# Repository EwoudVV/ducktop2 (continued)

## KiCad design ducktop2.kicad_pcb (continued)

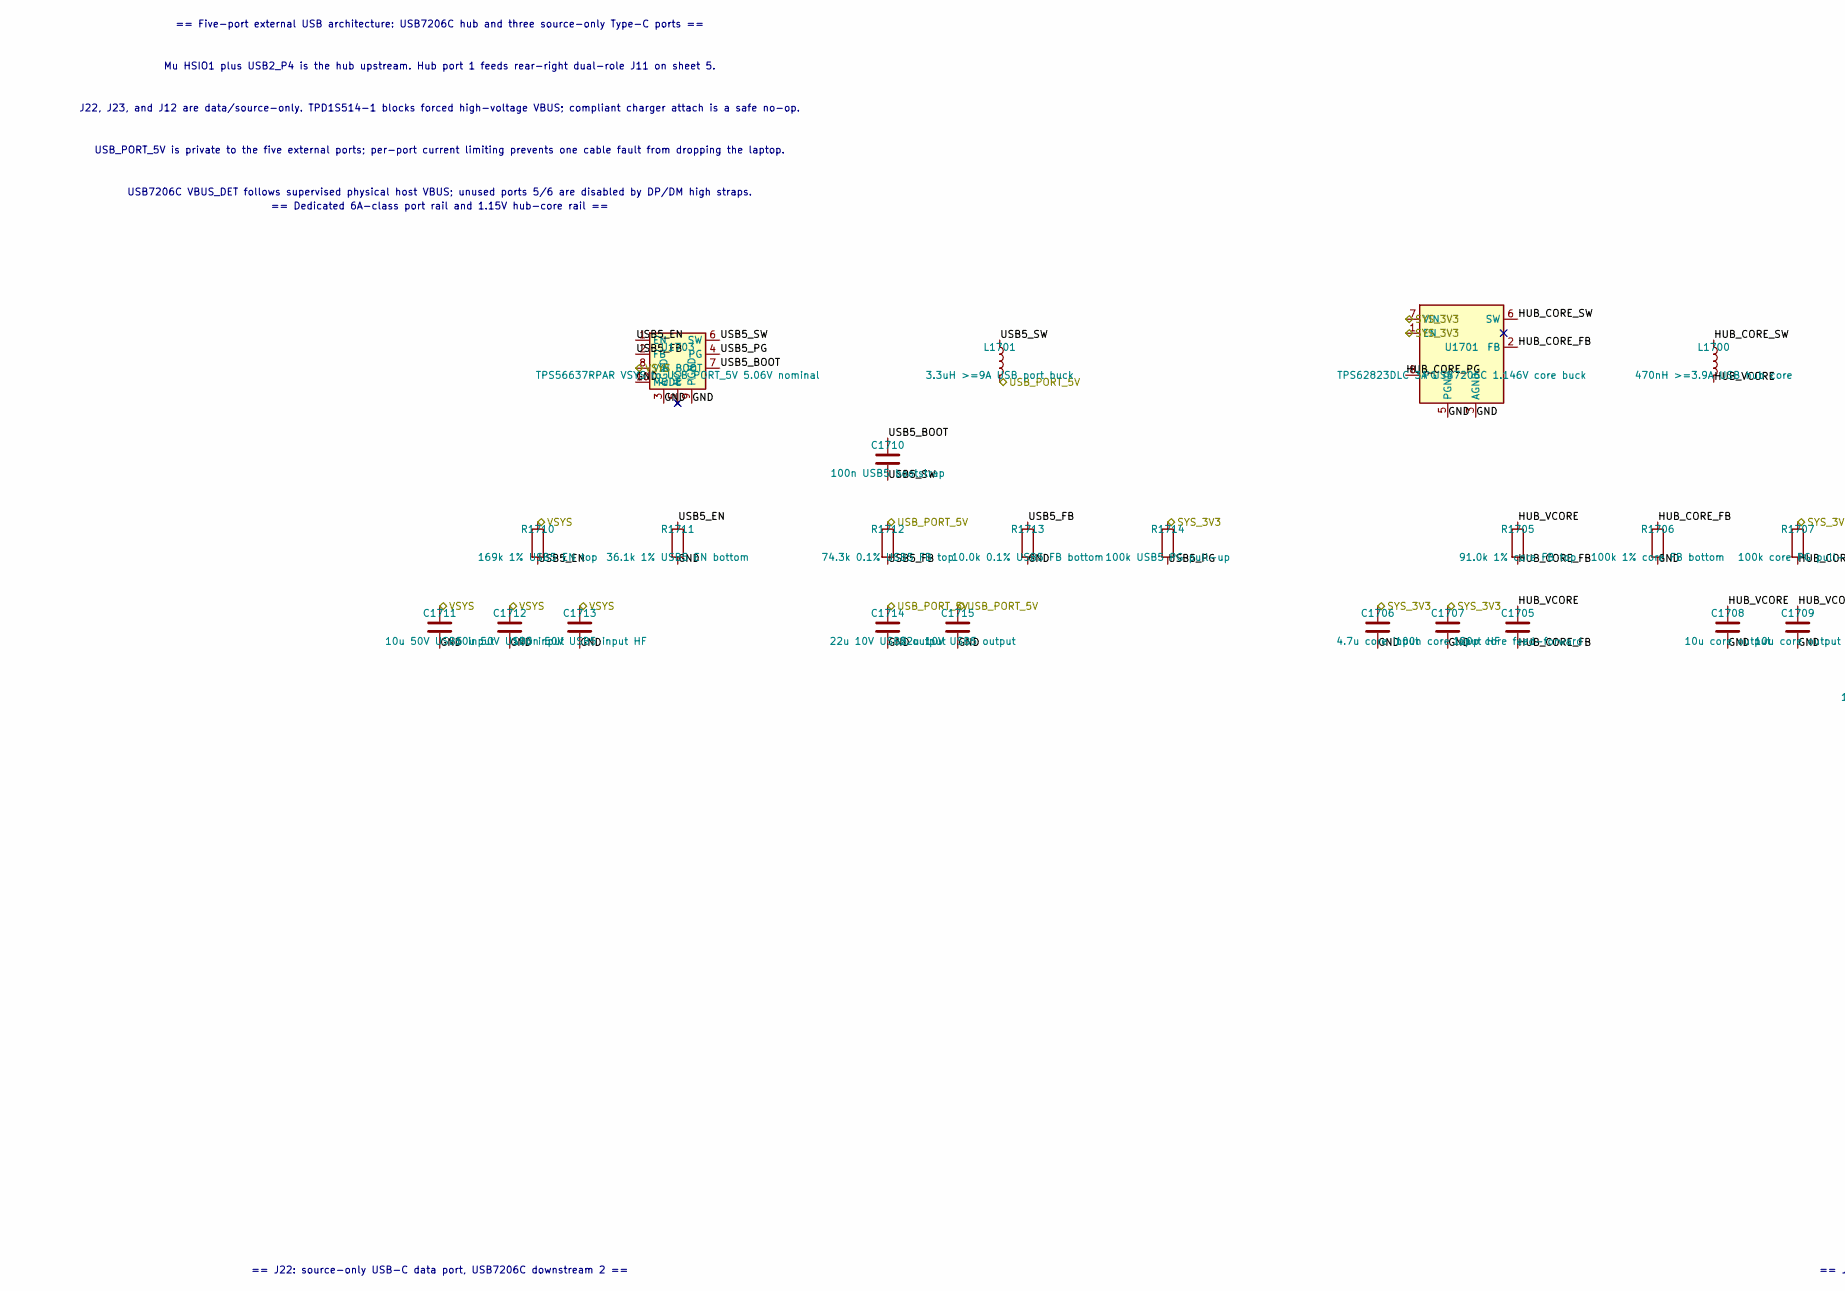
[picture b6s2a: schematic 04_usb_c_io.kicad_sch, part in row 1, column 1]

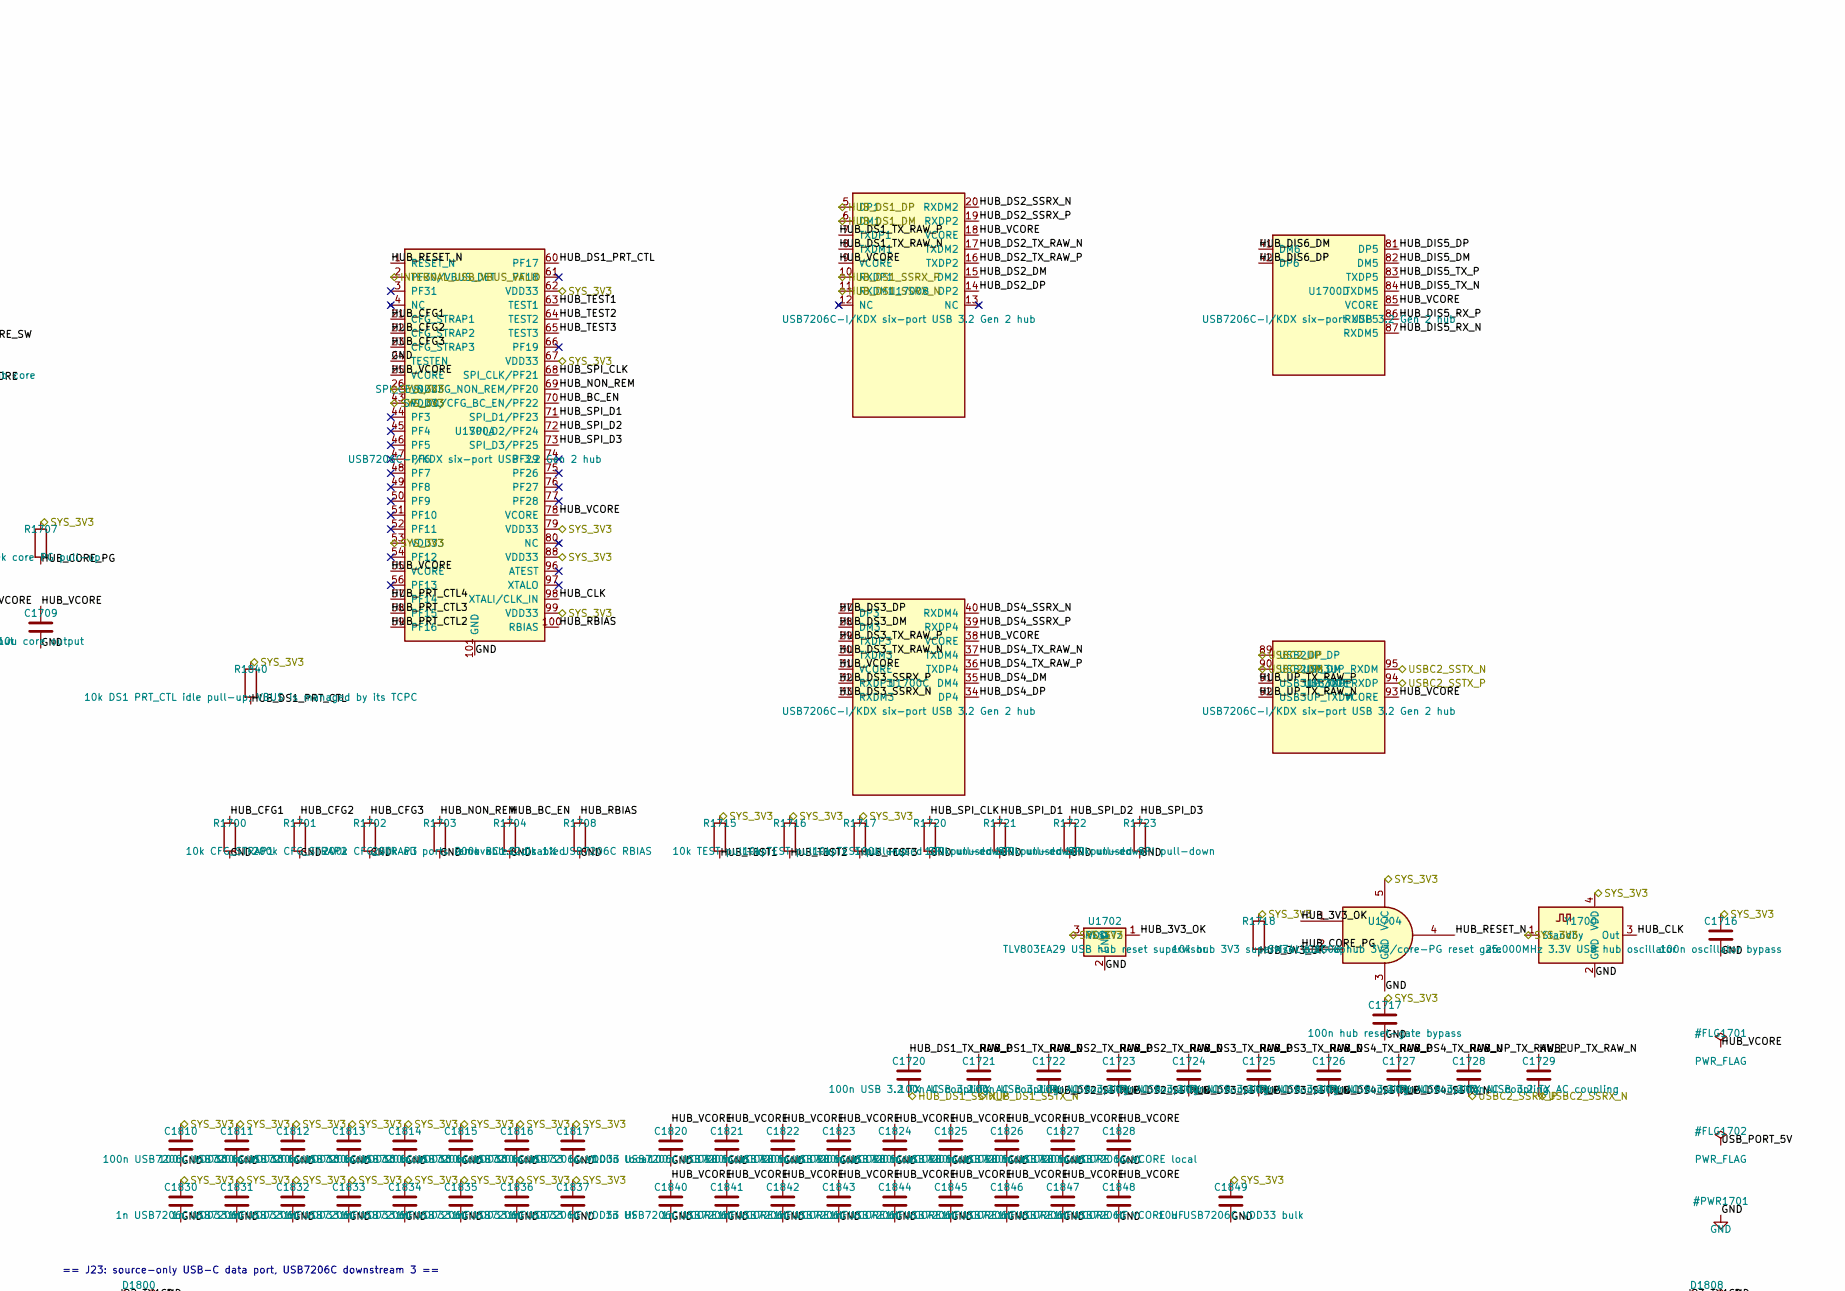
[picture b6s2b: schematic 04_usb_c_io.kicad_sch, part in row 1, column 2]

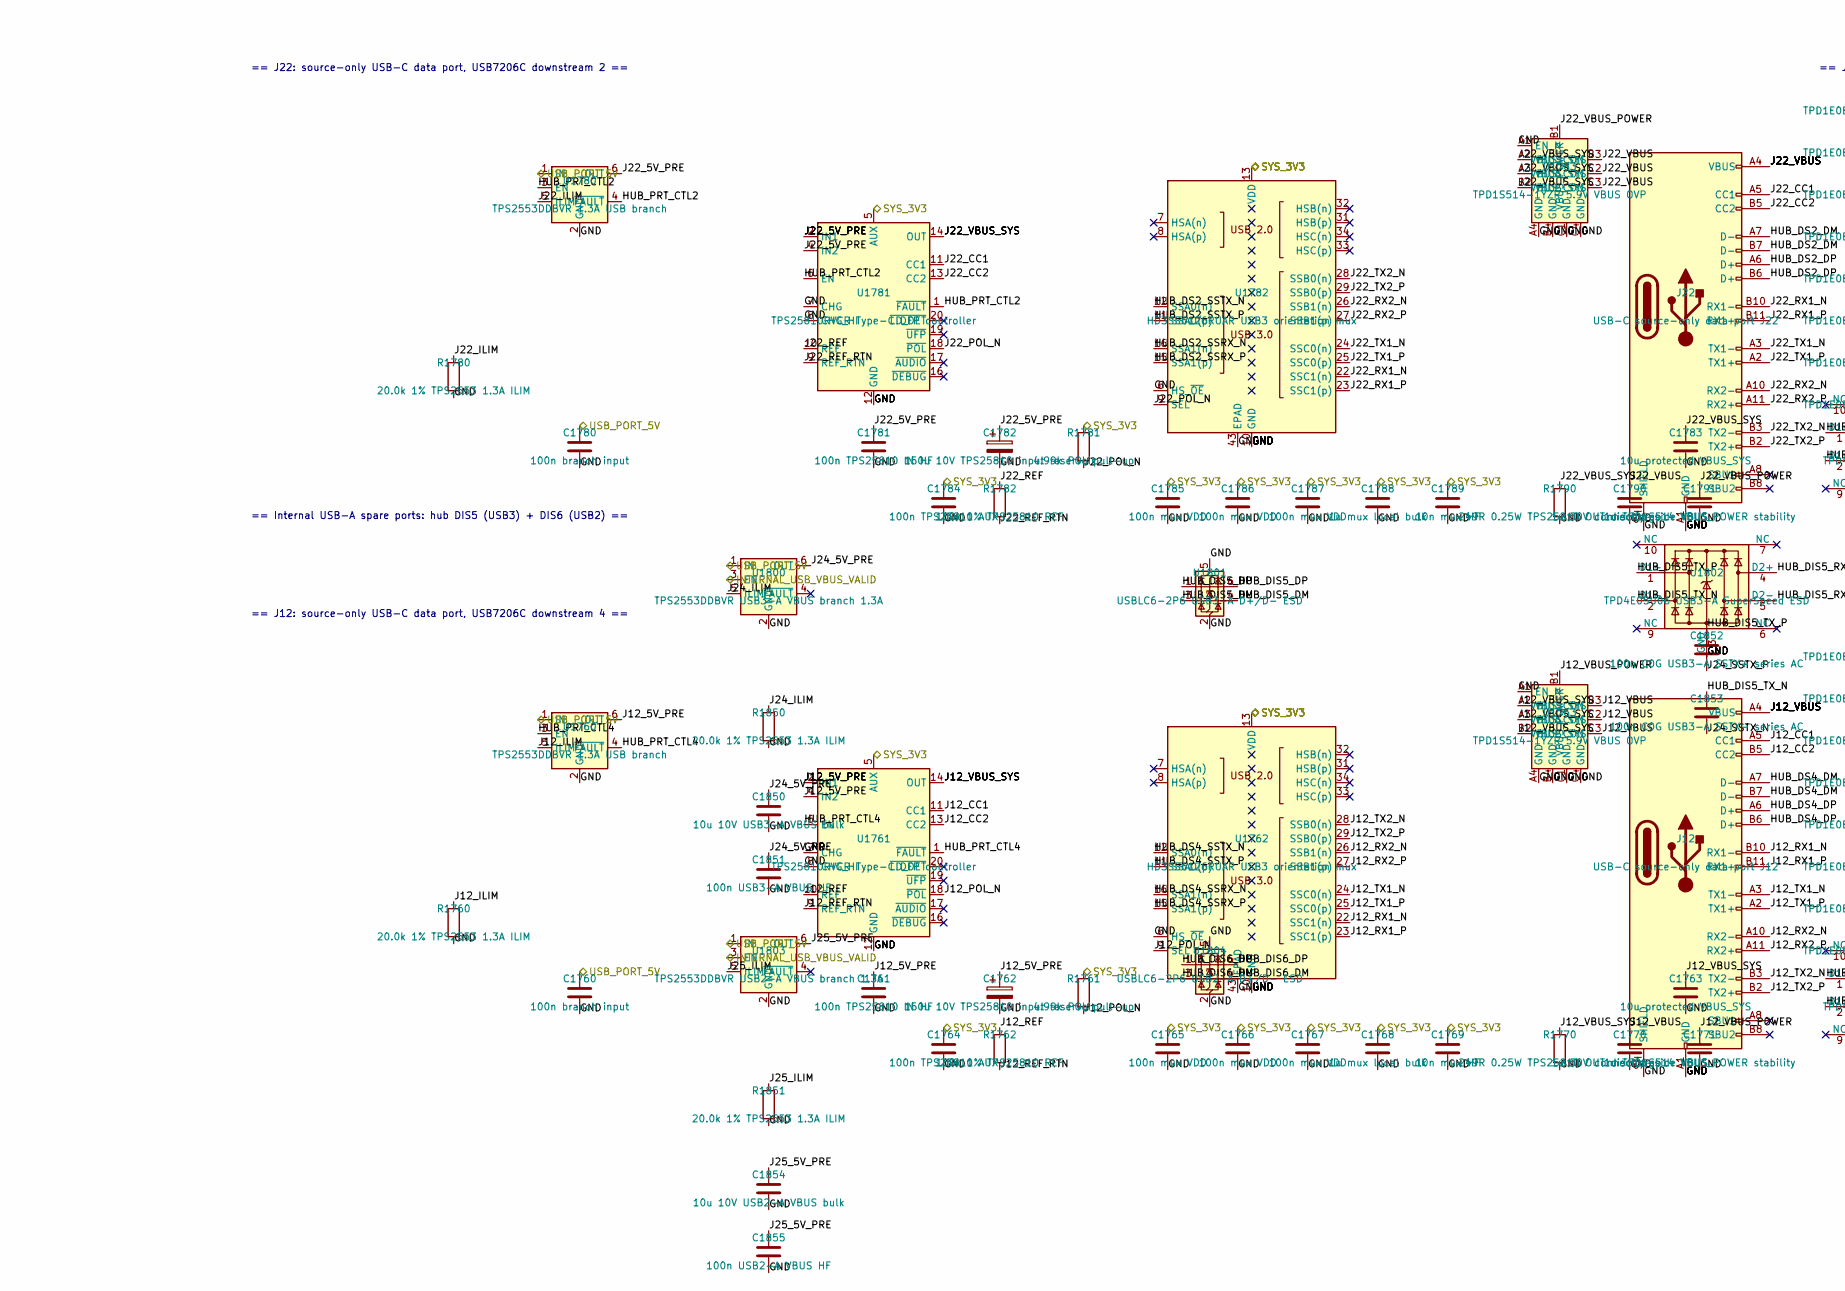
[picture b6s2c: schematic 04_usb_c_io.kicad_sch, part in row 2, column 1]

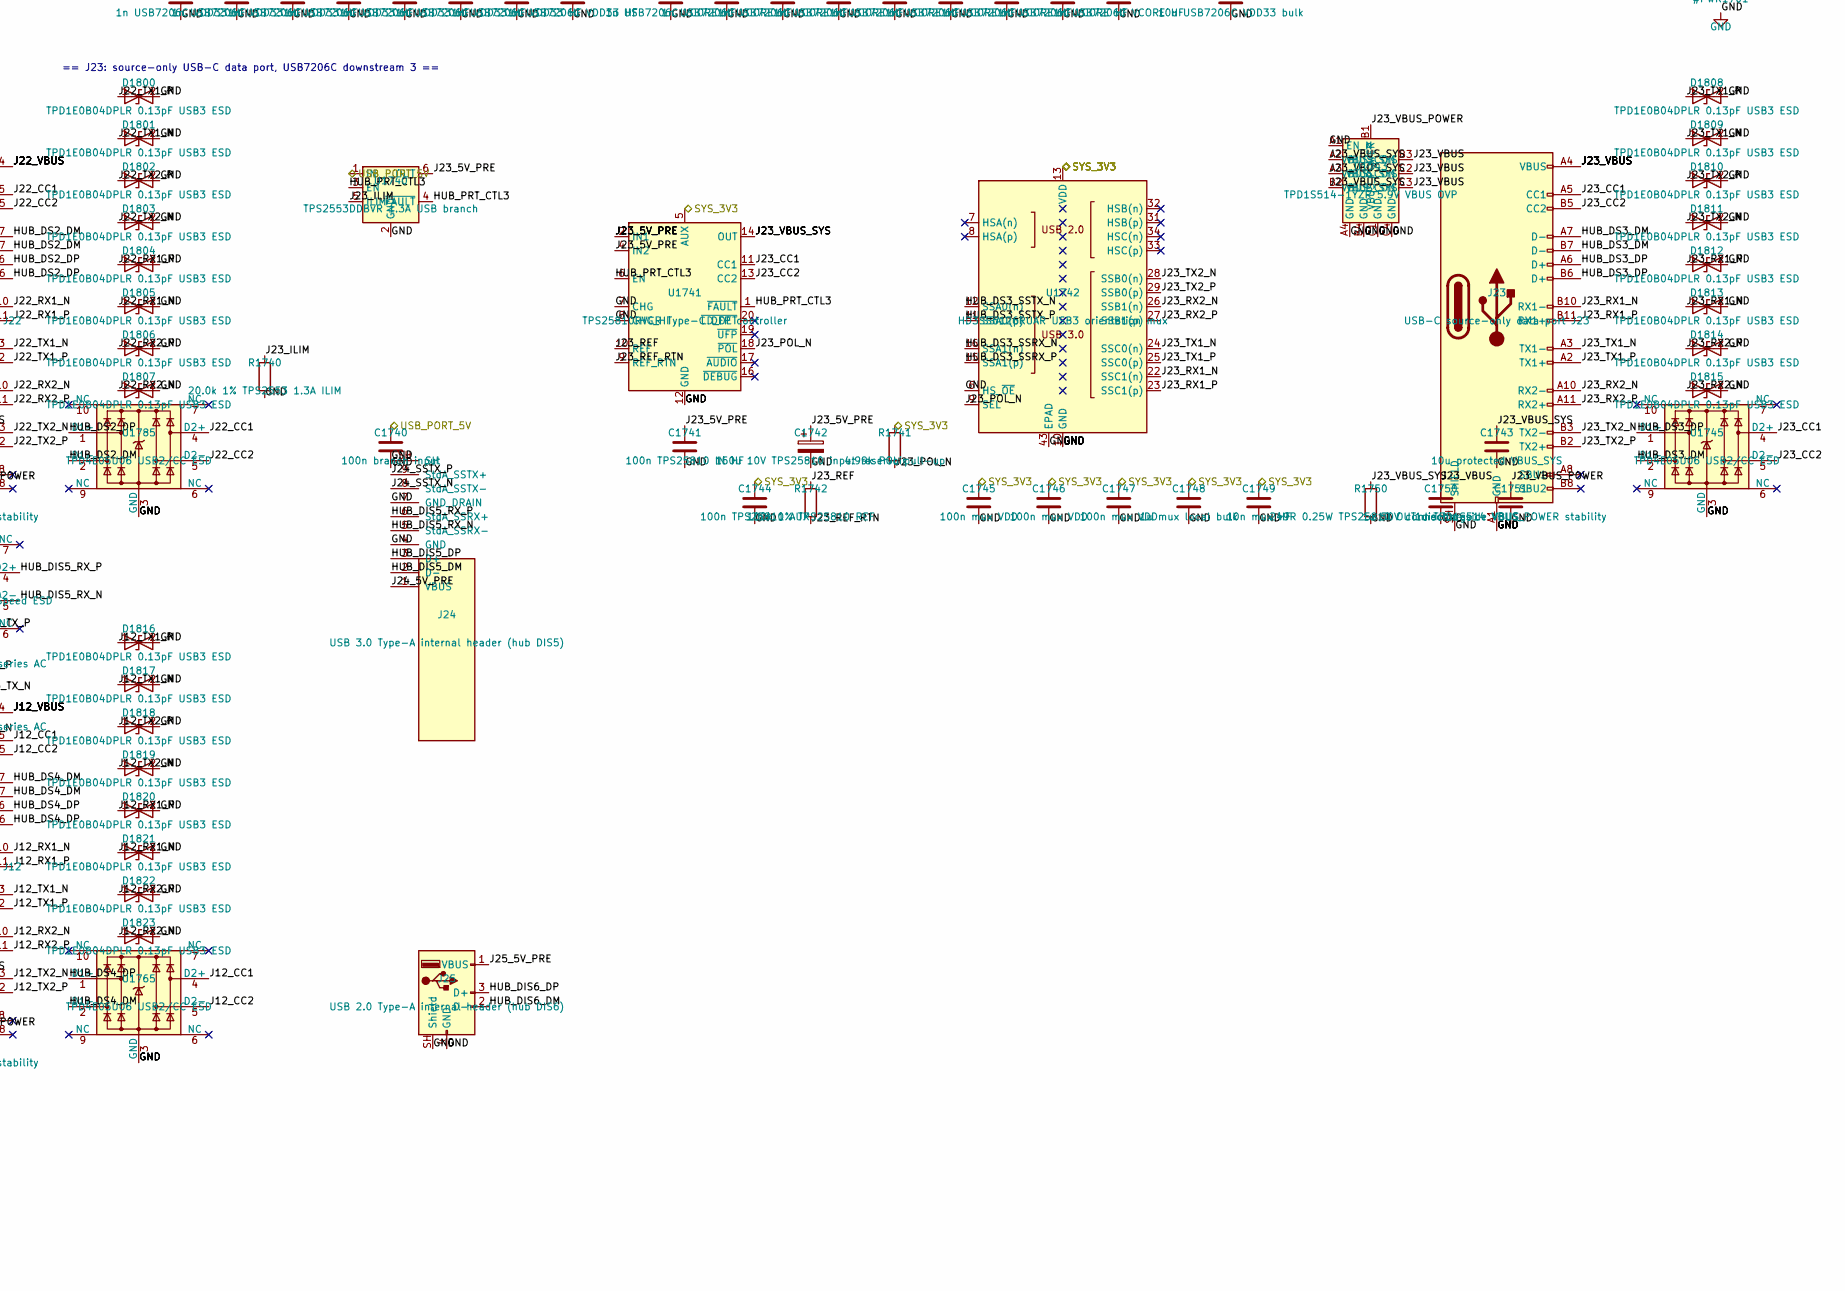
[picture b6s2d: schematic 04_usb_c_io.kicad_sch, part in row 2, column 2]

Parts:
C1705: 120p core feed-forward; C_0402_1005Metric; MPN GRM1555C1H121JA01D
C1706: 4.7u core input; C_0805_2012Metric; MPN GRM21BR71A475KA73L
C1707: 100n core input HF; C_0603_1608Metric; MPN GRM188R71H104KA93D
C1708, C1709: 10u core output; C_0805_2012Metric; MPN GRM21BR71A106KE51L
C1710: 100n USB5 bootstrap; C_0603_1608Metric; MPN GRM188R71H104KA93D
C1711, C1712: 10u 50V USB5 input; C_1206_3216Metric; MPN CGA5L1X7R1H106K160AC
C1713: 100n 50V USB5 input HF; C_0603_1608Metric; MPN GRM188R71H104KA93D
C1714, C1715: 22u 10V USB5 output; C_1210_3225Metric; MPN GRM32ER71A226KE20L
C1716: 100n oscillator bypass; C_0603_1608Metric; MPN GRM188R71H104KA93D
C1717: 100n hub reset-gate bypass; C_0603_1608Metric; MPN GRM188R71H104KA93D
C1720, C1721, C1722, C1723, C1724, C1725, C1726, C1727, C1728, C1729: 100n USB 3.2 TX AC coupling; C_0402_1005Metric; MPN GRM155R71C104KA88D
C1740, C1760, C1780: 100n branch input; C_0603_1608Metric; MPN GRM188R71H104KA93D
C1741, C1761, C1781: 100n TPS25810 IN HF; C_0603_1608Metric; MPN GRM188R71H104KA93D
C1742, C1762, C1782: 150u 10V TPS25810 input reservoir; CP_EIA-7343-31_Kemet-D; MPN T520D157M010ATE025
C1743, C1763, C1783: 10u protected VBUS_SYS; C_1206_3216Metric; MPN GRM31CR71A106KA01L
C1744, C1764, C1784: 100n TPS25810 AUX; C_0603_1608Metric; MPN GRM188R71H104KA93D
C1745, C1746, C1747, C1765, C1766, C1767, C1785, C1786, C1787: 100n mux VDD; C_0603_1608Metric; MPN GRM188R71H104KA93D
C1748, C1768, C1788: 1u mux local bulk; C_0603_1608Metric; MPN GRM188R71A105KA61D
C1749, C1769, C1789: 10n mux HF; C_0402_1005Metric; MPN GRM155R71H103KA88D
C1750, C1770, C1790: 1u 50V connector-side VBUS; C_0805_2012Metric; MPN GRM21BR71H105KA12L
C1751, C1771, C1791: 1u TPD1S514 VBUS_POWER stability; C_0603_1608Metric; MPN GRM188R71A105KA61D
C1810, C1811, C1812, C1813, C1814, C1815, C1816, C1817: 100n USB7206C VDD33 local; C_0603_1608Metric; MPN GRM188R71H104KA93D
C1820, C1821, C1822, C1823, C1824, C1825, C1826, C1827, C1828: 100n USB7206C VCORE local; C_0603_1608Metric; MPN GRM188R71H104KA93D
C1830, C1831, C1832, C1833, C1834, C1835, C1836, C1837: 1n USB7206C VDD33 HF; C_0402_1005Metric; MPN GRM155R71H102KA01D
C1840, C1841, C1842, C1843, C1844, C1845, C1846, C1847, C1848: 1n USB7206C VCORE HF; C_0402_1005Metric; MPN GRM155R71H102KA01D
C1849: 10u USB7206C VDD33 bulk; C_0805_2012Metric; MPN GRM21BR71A106KE51L
C1850: 10u 10V USB3-A VBUS bulk; C_1206_3216Metric; MPN GRM21BR71A106KA73L
C1851: 100n USB3-A VBUS HF; C_0603_1608Metric; MPN GRM188R71H104KA93D
C1852: 100n C0G USB3-A SSTX+ series AC; C_0402_1005Metric; MPN GRM1555C1H101JA01D
C1853: 100n C0G USB3-A SSTX- series AC; C_0402_1005Metric; MPN GRM1555C1H101JA01D
C1854: 10u 10V USB2-A VBUS bulk; C_1206_3216Metric; MPN GRM21BR71A106KA73L
C1855: 100n USB2-A VBUS HF; C_0603_1608Metric; MPN GRM188R71H104KA93D
D1800, D1801, D1802, D1803, D1804, D1805, D1806, D1807, D1808, D1809, D1810, D1811, D1812, D1813, D1814, D1815, D1816, D1817, D1818, D1819, D1820, D1821, D1822, D1823: TPD1E0B04DPLR 0.13pF USB3 ESD; D_0201_0603Metric; MPN TPD1E0B04DPLR
J12: USB-C source-only data port J12; USB_C_Receptacle_Molex_105450-0101; MPN 105450-0101
J22: USB-C source-only data port J22; USB_C_Receptacle_Molex_105450-0101; MPN 105450-0101
J23: USB-C source-only data port J23; USB_C_Receptacle_Molex_105450-0101; MPN 105450-0101
J24: USB 3.0 Type-A internal header (hub DIS5); USB_A_Receptacle_XKB_U231-091N-4BLRA00-S; MPN U231-091N-4BLRA00-S
J25: USB 2.0 Type-A internal header (hub DIS6); USB_A_Receptacle_GCT_USB1046; MPN USB1046-GF-L
L1700: 470nH >=3.9A USB hub core; TDK_TFM201610; MPN TFM201610ALMA-R47MTAA
L1701: 3.3uH >=9A USB port buck; L_Coilcraft_XAL7070-XXX; MPN XAL7070-332MEC
R1700: 10k CFG_STRAP1; R_0603_1608Metric; MPN RC0603FR-0710KL
R1701: 200k CFG_STRAP2; R_0603_1608Metric; MPN RC0603FR-07200KL
R1702: 200k CFG_STRAP3; R_0603_1608Metric; MPN RC0603FR-07200KL
R1703: 200k all ports removable; R_0603_1608Metric; MPN RC0603FR-07200KL
R1704: 200k BC1.2 disabled; R_0603_1608Metric; MPN RC0603FR-07200KL
R1705: 91.0k 1% core FB top; R_0603_1608Metric; MPN RC0603FR-0791KL
R1706: 100k 1% core FB bottom; R_0603_1608Metric; MPN RC0603FR-07100KL
R1707: 100k core PG pull-up; R_0603_1608Metric; MPN RC0603FR-07100KL
R1708: 12.0k 1% USB7206C RBIAS; R_0603_1608Metric; MPN RC0603FR-0712KL
R1710: 169k 1% USB5 EN top; R_0603_1608Metric; MPN RC0603FR-07169KL
R1711: 36.1k 1% USB5 EN bottom; R_0603_1608Metric; MPN RC0603FR-0736K1L
R1712: 74.3k 0.1% USB5 FB top; R_0603_1608Metric; MPN RT0603BRD0743KL
R1713: 10.0k 0.1% USB5 FB bottom; R_0603_1608Metric; MPN RT0603BRD0710KL
R1714: 100k USB5 PG pull-up; R_0603_1608Metric; MPN RC0603FR-07100KL
R1715, R1716, R1717: 10k TEST pull-up; R_0603_1608Metric; MPN RC0603FR-0710KL
R1718: 10k hub 3V3 supervisor pull-up; R_0603_1608Metric; MPN RC0603FR-0710KL
R1720, R1721, R1722, R1723: 100k unused SPI pull-down; R_0603_1608Metric; MPN RC0603FR-07100KL
R1740, R1760, R1780, R1850, R1851: 20.0k 1% TPS2553 1.3A ILIM; R_0603_1608Metric; MPN RC0603FR-0720KL
R1741, R1761, R1781: 4.99k POL pull-up; R_0603_1608Metric; MPN RC0603FR-074K99L
R1742, R1762, R1782: 100k 1% TPS25810 REF; R_0603_1608Metric; MPN RC0603FR-07100KL
R1750, R1770, R1790: 249R 0.25W TPS25810 OUT discharge; R_1206_3216Metric; MPN RC1206FR-07249RL
R1840: 10k DS1 PRT_CTL idle pull-up; VBUS is managed by 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; R_0603_1608Metric; MPN RC0603FR-0710KL
U1700: USB7206C-I/KDX six-port USB 3.2 Gen 2 hub; VQFN-100-1EP_12x12mm_P0.4mm_EP8x8mm_ThermalVias; MPN USB7206C-I/KDX
U1701: TPS62823DLC 3A USB7206C 1.146V core buck; Texas_VSON-HR-8_1.5x2mm_P0.5mm; MPN TPS62823DLC
U1702: TLV803EA29 USB hub reset supervisor; SOT-23-3; MPN TLV803EA29RDBZR
U1703: TPS56637RPAR VSYS to USB_PORT_5V 5.06V nominal; Texas_RPA0010A_VQFN-HR-10_3x3mm; MPN TPS56637RPAR
U1704: SN74LVC1G08 hub 3V3/core-PG reset gate; SOT-23-5; MPN SN74LVC1G08DBVR
U1740, U1760, U1780: TPS2553DDBVR 1.3A USB branch; SOT-23-6; MPN TPS2553DDBVR
U1741, U1761, U1781: TPS25810RVCR Type-C DFP controller; Texas_RVC0020A_WQFN-20-1EP_3x4mm_P0.5mm_EP1.6x2.6mm; MPN TPS25810RVCR
U1742, U1762, U1782: HD3SS6126RUAR USB3 orientation mux; WQFN-42-1EP_3.5x9mm_P0.5mm_EP2.05x7.55mm_ThermalVias; MPN HD3SS6126RUAR
U1743, U1763, U1783: TPD1S514-1YZR 5.9V VBUS OVP; Texas_TPD1S514_YZ_WCSP-12_1.99x1.29mm_P0.5mm; MPN TPD1S514-1YZR
U1745, U1765, U1785: TPD4E05U06 USB2/CC ESD; USON-10_2.5x1.0mm_P0.5mm; MPN TPD4E05U06DQAR
U1800: TPS2553DDBVR USB3-A VBUS branch 1.3A; SOT-23-6; MPN TPS2553DDBVR
U1801: USBLC6-2P6 USB3-A D+/D- ESD; SOT-666; MPN USBLC6-2P6
U1802: TPD4E05U06 USB3-A SuperSpeed ESD; USON-10_2.5x1.0mm_P0.5mm; MPN TPD4E05U06DQAR
U1803: TPS2553DDBVR USB2-A VBUS branch 1.3A; SOT-23-6; MPN TPS2553DDBVR
U1804: USBLC6-2P6 USB2-A D+/D- ESD; SOT-666; MPN USBLC6-2P6
Y1700: 25.000MHz 3.3V USB hub oscillator; Oscillator_SMD_Abracon_ASDMB-4Pin_2.5x2.0mm; MPN ASDMB-25.000MHZ-LC-T

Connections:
/HUB_DS1_DM: U1700.6 (DM1); also elsewhere on the board
/HUB_DS1_DP: U1700.5 (DP1); also elsewhere on the board
/HUB_DS1_SSRX_N: U1700.11 (RXDM1); also elsewhere on the board
/HUB_DS1_SSRX_P: U1700.10 (RXDP1); also elsewhere on the board
/HUB_DS1_SSTX_N: C1721.2; also elsewhere on the board
/HUB_DS1_SSTX_P: C1720.2; also elsewhere on the board
/INTERNAL_USB_VBUS_VALID: U1700.2 (PF30/VBUS_DET), U1800.3 (EN), U1803.3 (EN); also elsewhere on the board
/Native USB-C I/O/HUB_3V3_OK: R1718.2, U1702.1 (RESETz), U1704.1
/Native USB-C I/O/HUB_BC_EN: R1704.1, U1700.70 (SPI_D0/CFG_BC_EN/PF22)
/Native USB-C I/O/HUB_CFG1: R1700.1, U1700.21 (CFG_STRAP1)
/Native USB-C I/O/HUB_CFG2: R1701.1, U1700.22 (CFG_STRAP2)
/Native USB-C I/O/HUB_CFG3: R1702.1, U1700.23 (CFG_STRAP3)
/Native USB-C I/O/HUB_CLK: U1700.98 (XTALI/CLK_IN), Y1700.3 (Out)
/Native USB-C I/O/HUB_CORE_FB: C1705.2, R1705.2, R1706.1, U1701.2 (FB)
/Native USB-C I/O/HUB_CORE_PG: R1707.2, U1701.8 (PG), U1704.2
/Native USB-C I/O/HUB_CORE_SW: L1700.1, U1701.6 (SW)
/Native USB-C I/O/HUB_DIS5_DM: J24.2 (D-), U1700.82 (DM5), U1801.3 (I/O2), U1801.4 (I/O2)
/Native USB-C I/O/HUB_DIS5_DP: J24.3 (D+), U1700.81 (DP5), U1801.1 (I/O1), U1801.6 (I/O1)
/Native USB-C I/O/HUB_DIS5_RX_N: J24.5 (StdA_SSRX-), U1700.87 (RXDM5), U1802.5 (D2-)
/Native USB-C I/O/HUB_DIS5_RX_P: J24.6 (StdA_SSRX+), U1700.86 (RXDP5), U1802.4 (D2+)
/Native USB-C I/O/HUB_DIS5_TX_N: C1853.1, U1700.84 (TXDM5), U1802.2 (D1-)
/Native USB-C I/O/HUB_DIS5_TX_P: C1852.1, U1700.83 (TXDP5), U1802.1 (D1+)
/Native USB-C I/O/HUB_DIS6_DM: J25.2 (D-), U1700.41 (DM6), U1804.3 (I/O2), U1804.4 (I/O2)
/Native USB-C I/O/HUB_DIS6_DP: J25.3 (D+), U1700.42 (DP6), U1804.1 (I/O1), U1804.6 (I/O1)
/Native USB-C I/O/HUB_DS1_PRT_CTL: R1840.2, U1700.60 (PF17)
/Native USB-C I/O/HUB_DS1_TX_RAW_N: C1721.1, U1700.8 (TXDM1)
/Native USB-C I/O/HUB_DS1_TX_RAW_P: C1720.1, U1700.7 (TXDP1)
/Native USB-C I/O/HUB_DS2_DM: J22.A7 (D-), J22.B7 (D-), U1700.15 (DM2), U1785.2 (D1-)
/Native USB-C I/O/HUB_DS2_DP: J22.A6 (D+), J22.B6 (D+), U1700.14 (DP2), U1785.1 (D1+)
/Native USB-C I/O/HUB_DS2_SSRX_N: U1700.20 (RXDM2), U1782.16 (SSA1(n))
/Native USB-C I/O/HUB_DS2_SSRX_P: U1700.19 (RXDP2), U1782.15 (SSA1(p))
/Native USB-C I/O/HUB_DS2_SSTX_N: C1723.2, U1782.12 (SSA0(n))
/Native USB-C I/O/HUB_DS2_SSTX_P: C1722.2, U1782.11 (SSA0(p))
/Native USB-C I/O/HUB_DS2_TX_RAW_N: C1723.1, U1700.17 (TXDM2)
/Native USB-C I/O/HUB_DS2_TX_RAW_P: C1722.1, U1700.16 (TXDP2)
/Native USB-C I/O/HUB_DS3_DM: J23.A7 (D-), J23.B7 (D-), U1700.28 (DM3), U1745.2 (D1-)
/Native USB-C I/O/HUB_DS3_DP: J23.A6 (D+), J23.B6 (D+), U1700.27 (DP3), U1745.1 (D1+)
/Native USB-C I/O/HUB_DS3_SSRX_N: U1700.33 (RXDM3), U1742.16 (SSA1(n))
/Native USB-C I/O/HUB_DS3_SSRX_P: U1700.32 (RXDP3), U1742.15 (SSA1(p))
/Native USB-C I/O/HUB_DS3_SSTX_N: C1725.2, U1742.12 (SSA0(n))
/Native USB-C I/O/HUB_DS3_SSTX_P: C1724.2, U1742.11 (SSA0(p))
/Native USB-C I/O/HUB_DS3_TX_RAW_N: C1725.1, U1700.30 (TXDM3)
/Native USB-C I/O/HUB_DS3_TX_RAW_P: C1724.1, U1700.29 (TXDP3)
/Native USB-C I/O/HUB_DS4_DM: J12.A7 (D-), J12.B7 (D-), U1700.35 (DM4), U1765.2 (D1-)
/Native USB-C I/O/HUB_DS4_DP: J12.A6 (D+), J12.B6 (D+), U1700.34 (DP4), U1765.1 (D1+)
/Native USB-C I/O/HUB_DS4_SSRX_N: U1700.40 (RXDM4), U1762.16 (SSA1(n))
/Native USB-C I/O/HUB_DS4_SSRX_P: U1700.39 (RXDP4), U1762.15 (SSA1(p))
/Native USB-C I/O/HUB_DS4_SSTX_N: C1727.2, U1762.12 (SSA0(n))
/Native USB-C I/O/HUB_DS4_SSTX_P: C1726.2, U1762.11 (SSA0(p))
/Native USB-C I/O/HUB_DS4_TX_RAW_N: C1727.1, U1700.37 (TXDM4)
/Native USB-C I/O/HUB_DS4_TX_RAW_P: C1726.1, U1700.36 (TXDP4)
/Native USB-C I/O/HUB_NON_REM: R1703.1, U1700.69 (SPI_CE_N/CFG_NON_REM/PF20)
/Native USB-C I/O/HUB_PRT_CTL2: U1700.59 (PF16), U1780.3 (EN), U1780.4 (~FAULT), U1781.1 (~FAULT), U1781.6 (EN)
/Native USB-C I/O/HUB_PRT_CTL3: U1700.58 (PF15), U1740.3 (EN), U1740.4 (~FAULT), U1741.1 (~FAULT), U1741.6 (EN)
/Native USB-C I/O/HUB_PRT_CTL4: U1700.57 (PF14), U1760.3 (EN), U1760.4 (~FAULT), U1761.1 (~FAULT), U1761.6 (EN)
/Native USB-C I/O/HUB_RBIAS: R1708.1, U1700.100 (RBIAS)
/Native USB-C I/O/HUB_RESET_N: U1700.1 (RESET_N), U1704.4
/Native USB-C I/O/HUB_SPI_CLK: R1720.1, U1700.68 (SPI_CLK/PF21)
/Native USB-C I/O/HUB_SPI_D1: R1721.1, U1700.71 (SPI_D1/PF23)
/Native USB-C I/O/HUB_SPI_D2: R1722.1, U1700.72 (SPI_D2/PF24)
/Native USB-C I/O/HUB_SPI_D3: R1723.1, U1700.73 (SPI_D3/PF25)
/Native USB-C I/O/HUB_TEST1: R1715.2, U1700.63 (TEST1)
/Native USB-C I/O/HUB_TEST2: R1716.2, U1700.64 (TEST2)
/Native USB-C I/O/HUB_TEST3: R1717.2, U1700.65 (TEST3)
/Native USB-C I/O/HUB_UP_TX_RAW_N: C1729.1, U1700.92 (USB3UP_TXDM)
/Native USB-C I/O/HUB_UP_TX_RAW_P: C1728.1, U1700.91 (USB3UP_TXDP)
/Native USB-C I/O/HUB_VCORE: C1705.1, C1708.1, C1709.1, C1820.1, C1821.1, C1822.1, C1823.1, C1824.1, C1825.1, C1826.1, C1827.1, C1828.1, C1840.1, C1841.1, C1842.1, C1843.1, C1844.1, C1845.1, C1846.1, C1847.1, C1848.1, L1700.2, R1705.1, U1700.9 (VCORE), U1700.18 (VCORE), U1700.25 (VCORE), U1700.31 (VCORE), U1700.38 (VCORE), U1700.55 (VCORE), U1700.78 (VCORE), U1700.85 (VCORE), U1700.93 (VCORE)
/Native USB-C I/O/J12_5V_PRE: C1761.1, C1762.1, U1760.6 (OUT), U1761.2 (IN1), U1761.3 (IN1), U1761.4 (IN2)
/Native USB-C I/O/J12_CC1: J12.A5 (CC1), U1761.11 (CC1), U1765.4 (D2+)
/Native USB-C I/O/J12_CC2: J12.B5 (CC2), U1761.13 (CC2), U1765.5 (D2-)
/Native USB-C I/O/J12_ILIM: R1760.1, U1760.5 (ILIM)
/Native USB-C I/O/J12_POL_N: R1761.2, U1761.18 (~POL), U1762.9 (SEL)
/Native USB-C I/O/J12_REF: R1762.1, U1761.10 (REF)
/Native USB-C I/O/J12_REF_RTN: R1762.2, U1761.9 (REF_RTN)
/Native USB-C I/O/J12_RX1_N: D1821.1 (IO), J12.B10 (RX1-), U1762.22 (SSC1(n))
/Native USB-C I/O/J12_RX1_P: D1820.1 (IO), J12.B11 (RX1+), U1762.23 (SSC1(p))
/Native USB-C I/O/J12_RX2_N: D1823.1 (IO), J12.A10 (RX2-), U1762.26 (SSB1(n))
/Native USB-C I/O/J12_RX2_P: D1822.1 (IO), J12.A11 (RX2+), U1762.27 (SSB1(p))
/Native USB-C I/O/J12_TX1_N: D1817.1 (IO), J12.A3 (TX1-), U1762.24 (SSC0(n))
/Native USB-C I/O/J12_TX1_P: D1816.1 (IO), J12.A2 (TX1+), U1762.25 (SSC0(p))
/Native USB-C I/O/J12_TX2_N: D1819.1 (IO), J12.B3 (TX2-), U1762.28 (SSB0(n))
/Native USB-C I/O/J12_TX2_P: D1818.1 (IO), J12.B2 (TX2+), U1762.29 (SSB0(p))
/Native USB-C I/O/J12_VBUS: C1770.1, J12.A4 (VBUS), J12.A9 (VBUS), J12.B4 (VBUS), J12.B9 (VBUS), U1763.B3 (VBUS_CON), U1763.C2 (VBUS_CON), U1763.C3 (VBUS_CON)
/Native USB-C I/O/J12_VBUS_POWER: C1771.1, U1763.B1 (VBUS_POWER)
/Native USB-C I/O/J12_VBUS_SYS: C1763.1, R1770.1, U1761.14 (OUT), U1761.15 (OUT), U1763.A2 (VBUS_SYS), U1763.A3 (VBUS_SYS), U1763.B2 (VBUS_SYS)
/Native USB-C I/O/J22_5V_PRE: C1781.1, C1782.1, U1780.6 (OUT), U1781.2 (IN1), U1781.3 (IN1), U1781.4 (IN2)
/Native USB-C I/O/J22_CC1: J22.A5 (CC1), U1781.11 (CC1), U1785.4 (D2+)
/Native USB-C I/O/J22_CC2: J22.B5 (CC2), U1781.13 (CC2), U1785.5 (D2-)
/Native USB-C I/O/J22_ILIM: R1780.1, U1780.5 (ILIM)
/Native USB-C I/O/J22_POL_N: R1781.2, U1781.18 (~POL), U1782.9 (SEL)
/Native USB-C I/O/J22_REF: R1782.1, U1781.10 (REF)
/Native USB-C I/O/J22_REF_RTN: R1782.2, U1781.9 (REF_RTN)
/Native USB-C I/O/J22_RX1_N: D1805.1 (IO), J22.B10 (RX1-), U1782.22 (SSC1(n))
/Native USB-C I/O/J22_RX1_P: D1804.1 (IO), J22.B11 (RX1+), U1782.23 (SSC1(p))
/Native USB-C I/O/J22_RX2_N: D1807.1 (IO), J22.A10 (RX2-), U1782.26 (SSB1(n))
/Native USB-C I/O/J22_RX2_P: D1806.1 (IO), J22.A11 (RX2+), U1782.27 (SSB1(p))
/Native USB-C I/O/J22_TX1_N: D1801.1 (IO), J22.A3 (TX1-), U1782.24 (SSC0(n))
/Native USB-C I/O/J22_TX1_P: D1800.1 (IO), J22.A2 (TX1+), U1782.25 (SSC0(p))
/Native USB-C I/O/J22_TX2_N: D1803.1 (IO), J22.B3 (TX2-), U1782.28 (SSB0(n))
/Native USB-C I/O/J22_TX2_P: D1802.1 (IO), J22.B2 (TX2+), U1782.29 (SSB0(p))
/Native USB-C I/O/J22_VBUS: C1790.1, J22.A4 (VBUS), J22.A9 (VBUS), J22.B4 (VBUS), J22.B9 (VBUS), U1783.B3 (VBUS_CON), U1783.C2 (VBUS_CON), U1783.C3 (VBUS_CON)
/Native USB-C I/O/J22_VBUS_POWER: C1791.1, U1783.B1 (VBUS_POWER)
/Native USB-C I/O/J22_VBUS_SYS: C1783.1, R1790.1, U1781.14 (OUT), U1781.15 (OUT), U1783.A2 (VBUS_SYS), U1783.A3 (VBUS_SYS), U1783.B2 (VBUS_SYS)
/Native USB-C I/O/J23_5V_PRE: C1741.1, C1742.1, U1740.6 (OUT), U1741.2 (IN1), U1741.3 (IN1), U1741.4 (IN2)
/Native USB-C I/O/J23_CC1: J23.A5 (CC1), U1741.11 (CC1), U1745.4 (D2+)
/Native USB-C I/O/J23_CC2: J23.B5 (CC2), U1741.13 (CC2), U1745.5 (D2-)
/Native USB-C I/O/J23_ILIM: R1740.1, U1740.5 (ILIM)
/Native USB-C I/O/J23_POL_N: R1741.2, U1741.18 (~POL), U1742.9 (SEL)
/Native USB-C I/O/J23_REF: R1742.1, U1741.10 (REF)
/Native USB-C I/O/J23_REF_RTN: R1742.2, U1741.9 (REF_RTN)
/Native USB-C I/O/J23_RX1_N: D1813.1 (IO), J23.B10 (RX1-), U1742.22 (SSC1(n))
/Native USB-C I/O/J23_RX1_P: D1812.1 (IO), J23.B11 (RX1+), U1742.23 (SSC1(p))
/Native USB-C I/O/J23_RX2_N: D1815.1 (IO), J23.A10 (RX2-), U1742.26 (SSB1(n))
/Native USB-C I/O/J23_RX2_P: D1814.1 (IO), J23.A11 (RX2+), U1742.27 (SSB1(p))
/Native USB-C I/O/J23_TX1_N: D1809.1 (IO), J23.A3 (TX1-), U1742.24 (SSC0(n))
/Native USB-C I/O/J23_TX1_P: D1808.1 (IO), J23.A2 (TX1+), U1742.25 (SSC0(p))
/Native USB-C I/O/J23_TX2_N: D1811.1 (IO), J23.B3 (TX2-), U1742.28 (SSB0(n))
/Native USB-C I/O/J23_TX2_P: D1810.1 (IO), J23.B2 (TX2+), U1742.29 (SSB0(p))
/Native USB-C I/O/J23_VBUS: C1750.1, J23.A4 (VBUS), J23.A9 (VBUS), J23.B4 (VBUS), J23.B9 (VBUS), U1743.B3 (VBUS_CON), U1743.C2 (VBUS_CON), U1743.C3 (VBUS_CON)
/Native USB-C I/O/J23_VBUS_POWER: C1751.1, U1743.B1 (VBUS_POWER)
/Native USB-C I/O/J23_VBUS_SYS: C1743.1, R1750.1, U1741.14 (OUT), U1741.15 (OUT), U1743.A2 (VBUS_SYS), U1743.A3 (VBUS_SYS), U1743.B2 (VBUS_SYS)
/Native USB-C I/O/J24_5V_PRE: C1850.1, C1851.1, J24.1 (VBUS), U1800.6 (OUT)
/Native USB-C I/O/J24_ILIM: R1850.1, U1800.5 (ILIM)
/Native USB-C I/O/J24_SSTX_N: C1853.2, J24.8 (StdA_SSTX-)
/Native USB-C I/O/J24_SSTX_P: C1852.2, J24.9 (StdA_SSTX+)
/Native USB-C I/O/J25_5V_PRE: C1854.1, C1855.1, J25.1 (VBUS), U1803.6 (OUT)
/Native USB-C I/O/J25_ILIM: R1851.1, U1803.5 (ILIM)
/Native USB-C I/O/USB5_BOOT: C1710.1, U1703.7 (BOOT)
/Native USB-C I/O/USB5_EN: R1710.2, R1711.1, U1703.1 (EN)
/Native USB-C I/O/USB5_FB: R1712.2, R1713.1, U1703.2 (FB)
/Native USB-C I/O/USB5_PG: R1714.2, U1703.4 (PG)
/Native USB-C I/O/USB5_SW: C1710.2, L1701.1, U1703.6 (SW)
/SYS_3V3: C1706.1, C1707.1, C1716.1, C1717.1, C1744.1, C1745.1, C1746.1, C1747.1, C1748.1, C1749.1, C1764.1, C1765.1, C1766.1, C1767.1, C1768.1, C1769.1, C1784.1, C1785.1, C1786.1, C1787.1, C1788.1, C1789.1, C1810.1, C1811.1, C1812.1, C1813.1, C1814.1, C1815.1, C1816.1, C1817.1, C1830.1, C1831.1, C1832.1, C1833.1, C1834.1, C1835.1, C1836.1, C1837.1, C1849.1, R1707.1, R1714.1, R1715.1, R1716.1, R1717.1, R1718.1, R1741.1, R1761.1, R1781.1, R1840.1, U1700.26 (VDD33), U1700.43 (VDD33), U1700.53 (VDD33), U1700.62 (VDD33), U1700.67 (VDD33), U1700.79 (VDD33), U1700.88 (VDD33), U1700.99 (VDD33), U1701.1 (EN), U1701.7 (VIN), U1702.3 (VDD), U1704.5 (VCC), U1741.5 (AUX), U1742.13 (VDD), U1742.20 (VDD), U1742.30 (VDD), U1761.5 (AUX), U1762.13 (VDD), U1762.20 (VDD), U1762.30 (VDD), U1781.5 (AUX), U1782.13 (VDD), U1782.20 (VDD), U1782.30 (VDD), Y1700.1 (Standby), Y1700.4 (VDD); also elsewhere on the board
/USBC2_DM: U1700.90 (USB2UP_DM); also elsewhere on the board
/USBC2_DP: U1700.89 (USB2UP_DP); also elsewhere on the board
/USBC2_SSRX_N: C1729.2; also elsewhere on the board
/USBC2_SSRX_P: C1728.2; also elsewhere on the board
/USBC2_SSTX_N: U1700.95 (USB3UP_RXDM); also elsewhere on the board
/USBC2_SSTX_P: U1700.94 (USB3UP_RXDP); also elsewhere on the board
/USB_PORT_5V: C1714.1, C1715.1, C1740.1, C1760.1, C1780.1, L1701.2, R1712.1, U1740.1 (IN), U1760.1 (IN), U1780.1 (IN), U1800.1 (IN), U1803.1 (IN); also elsewhere on the board
/VSYS: C1711.1, C1712.1, C1713.1, R1710.1, U1703.8 (VIN); also elsewhere on the board
GND: C1706.2, C1707.2, C1708.2, C1709.2, C1711.2, C1712.2, C1713.2, C1714.2, C1715.2, C1716.2, C1717.2, C1740.2, C1741.2, C1742.2, C1743.2, C1744.2, C1745.2, C1746.2, C1747.2, C1748.2, C1749.2, C1750.2, C1751.2, C1760.2, C1761.2, C1762.2, C1763.2, C1764.2, C1765.2, C1766.2, C1767.2, C1768.2, C1769.2, C1770.2, C1771.2, C1780.2, C1781.2, C1782.2, C1783.2, C1784.2, C1785.2, C1786.2, C1787.2, C1788.2, C1789.2, C1790.2, C1791.2, C1810.2, C1811.2, C1812.2, C1813.2, C1814.2, C1815.2, C1816.2, C1817.2, C1820.2, C1821.2, C1822.2, C1823.2, C1824.2, C1825.2, C1826.2, C1827.2, C1828.2, C1830.2, C1831.2, C1832.2, C1833.2, C1834.2, C1835.2, C1836.2, C1837.2, C1840.2, C1841.2, C1842.2, C1843.2, C1844.2, C1845.2, C1846.2, C1847.2, C1848.2, C1849.2, C1850.2, C1851.2, C1854.2, C1855.2, D1800.2 (IO), D1801.2 (IO), D1802.2 (IO), D1803.2 (IO), D1804.2 (IO), D1805.2 (IO), D1806.2 (IO), D1807.2 (IO), D1808.2 (IO), D1809.2 (IO), D1810.2 (IO), D1811.2 (IO), D1812.2 (IO), D1813.2 (IO), D1814.2 (IO), D1815.2 (IO), D1816.2 (IO), D1817.2 (IO), D1818.2 (IO), D1819.2 (IO), D1820.2 (IO), D1821.2 (IO), D1822.2 (IO), D1823.2 (IO), J12.A1 (GND), J12.A12 (GND), J12.B1 (GND), J12.B12 (GND), J12.SH (SHIELD), J22.A1 (GND), J22.A12 (GND), J22.B1 (GND), J22.B12 (GND), J22.SH (SHIELD), J23.A1 (GND), J23.A12 (GND), J23.B1 (GND), J23.B12 (GND), J23.SH (SHIELD), J24.4 (GND), J24.7 (GND_DRAIN), J24.SH, J25.4 (GND), J25.SH (Shield), R1700.2, R1701.2, R1702.2, R1703.2, R1704.2, R1706.2, R1708.2, R1711.2, R1713.2, R1720.2, R1721.2, R1722.2, R1723.2, R1740.2, R1750.2, R1760.2, R1770.2, R1780.2, R1790.2, R1850.2, R1851.2, U1700.24 (TESTEN), U1700.101 (GND), U1701.3 (AGND), U1701.5 (PGND), U1702.2 (GND), U1703.3 (AGND), U1703.9 (PGND), U1703.10 (MODE), U1704.3 (GND), U1740.2 (GND), U1741.7 (CHG), U1741.8 (CHG_HI), U1741.12 (GND), U1741.21 (GND), U1742.6 (HS_~OE), U1742.10 (GND), U1742.14 (GND), U1742.17 (GND), U1742.19 (GND), U1742.21 (GND), U1742.43 (EPAD), U1743.A1 (EN_N), U1743.A4 (GND), U1743.B4 (GND), U1743.C1 (GND), U1743.C4 (GND), U1745.3 (GND), U1745.8 (GND), U1760.2 (GND), U1761.7 (CHG), U1761.8 (CHG_HI), U1761.12 (GND), U1761.21 (GND), U1762.6 (HS_~OE), U1762.10 (GND), U1762.14 (GND), U1762.17 (GND), U1762.19 (GND), U1762.21 (GND), U1762.43 (EPAD), U1763.A1 (EN_N), U1763.A4 (GND), U1763.B4 (GND), U1763.C1 (GND), U1763.C4 (GND), U1765.3 (GND), U1765.8 (GND), U1780.2 (GND), U1781.7 (CHG), U1781.8 (CHG_HI), U1781.12 (GND), U1781.21 (GND), U1782.6 (HS_~OE), U1782.10 (GND), U1782.14 (GND), U1782.17 (GND), U1782.19 (GND), U1782.21 (GND), U1782.43 (EPAD), U1783.A1 (EN_N), U1783.A4 (GND), U1783.B4 (GND), U1783.C1 (GND), U1783.C4 (GND), U1785.3 (GND), U1785.8 (GND), U1800.2 (GND), U1801.2 (GND), U1801.5 (VBUS), U1802.3 (GND), U1802.8 (GND), U1803.2 (GND), U1804.2 (GND), U1804.5 (VBUS), Y1700.2 (GND); also elsewhere on the board

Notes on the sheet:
== Five-port external USB architecture: USB7206C hub and three source-only Type-C ports ==
Mu HSIO1 plus USB2_P4 is the hub upstream. Hub port 1 feeds rear-right dual-role J11 on sheet 5.
J22, J23, and J12 are data/source-only. TPD1S514-1 blocks forced high-voltage VBUS; compliant charger attach is a safe no-op.
USB_PORT_5V is private to the five external ports; per-port current limiting prevents one cable fault from dropping the laptop.
USB7206C VBUS_DET follows supervised physical host VBUS; unused ports 5/6 are disabled by DP/DM high straps.
== Dedicated 6A-class port rail and 1.15V hub-core rail ==
== Internal USB-A spare ports: hub DIS5 (USB3) + DIS6 (USB2) ==
== J22: source-only USB-C data port, USB7206C downstream 2 ==
== J23: source-only USB-C data port, USB7206C downstream 3 ==
== J12: source-only USB-C data port, USB7206C downstream 4 ==
